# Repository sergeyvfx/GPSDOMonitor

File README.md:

# GPSDO Monitor

A tiny module which is connecting to a databus of GPSDO modules with the goal
to visualize when the PLL is locked, GPS time is stabilized and things like
this. Pretty much minimized version of Lady Heather from John Miles, KE5FX
implemented in microcontroller.

## Licensing

All the work done and implemented for this project is licensed under the
terms of MIT license.

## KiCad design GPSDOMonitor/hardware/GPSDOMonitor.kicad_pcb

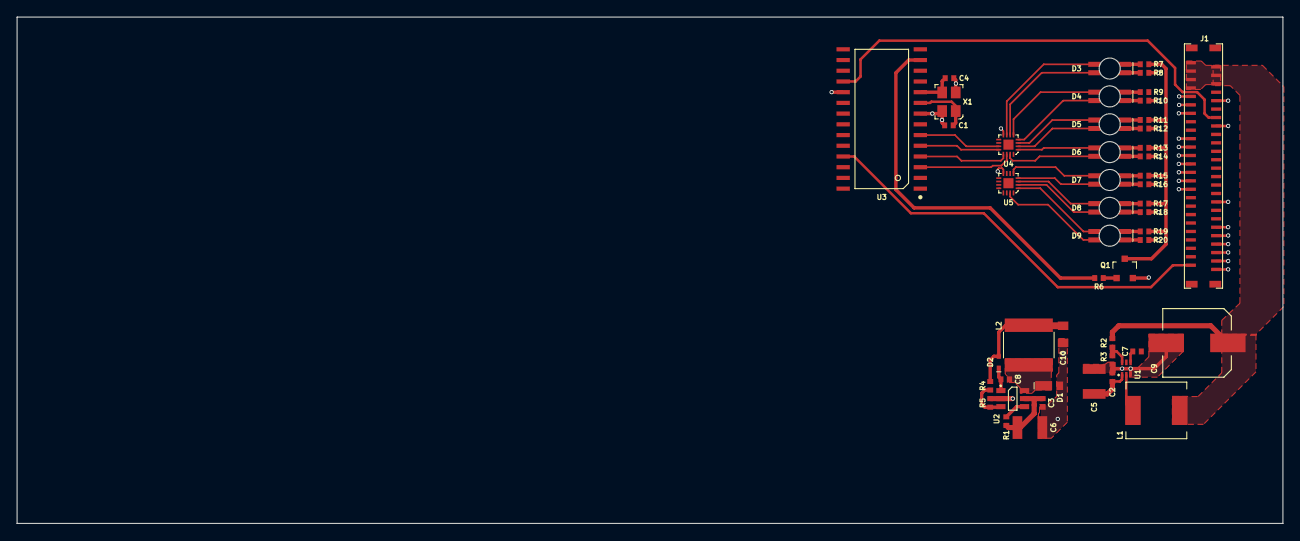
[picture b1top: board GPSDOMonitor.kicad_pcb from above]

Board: 2 copper layers, 150.0 x 60.0 mm, 49 parts (0 on the bottom side), 51 nets.

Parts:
C1, C4: CBR04C409B5GAC; C_0402_1005Metric
C2, C3, C7, C8: UMK105B7104KV-FR; C_0402_1005Metric
C5, C6: UMK325AB7106KM-P; C_1210_3225Metric
C9: A768KE686M1GLAE038; CP_Elec_KEMET_8mm
C10: EMK212BB7106KG-T; C_0805_2012Metric
D1: SS14HE; SOD-323HE
D2: 1N914BWT; SOD-523
D3, D4, D5, D6, D7, D8, D9: 5977703607F
J1: F31S-1A7L1-11050
L1: ASPI-7318-4R7M-T; ASPI-7318
L2: NR6028T150M; NR6028
Q1: MMBT3904LT1G; SOT-23
R1: CRG0402ZR; R_0402_1005Metric
R2: CRGCQ0402F82K; R_0402_1005Metric
R3, R5: CRGCQ0402F10K; R_0402_1005Metric
R4: CRGCQ0402F33K; R_0402_1005Metric
R6: CRGCQ0402F1K0; R_0402_1005Metric
R7, R8, R9, R10, R11, R12, R13, R14, R15, R16, R17, R18, R19, R20: CRGCQ0402F68R; R_0402_1005Metric
U1: TPS563231DRLR; SOT-563
U2: MCP16301T-I_CHY; SOT-23-6
U3: PIC18LF2550-ISO; SOIC-28_Width7.50mm_Pitch1.27mm
U4, U5: SN74HC595BRWNR; X1QFN-16_EP_2.5x2.5mm
X1: ABM8W-20.0000MHZ-4-K1Z-T3; Crystal_SMD_4Pin_3.2x2.5mm

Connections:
+3V3: C10.1, D2.2, L2.2, R4.1, U3.20, U4.10, U5.10
+5V5: C9.1, J1.1, J1.2, J1.3, J1.4, J1.5, J1.6, J1.7, L1.2, R2.1
+12V: C2.1, C3.1, C5.1, C6.1, R1.1, U1.1, U1.5, U2.5
/LED_PWM: R6.2, U3.13
/OE: U3.4, U4.13, U5.13
/RCLK: U3.5, U4.12, U5.12
/SER: U3.3, U4.14
/SRCLK: U3.6, U4.11, U5.11
GND: C1.2, C2.2, C3.2, C4.2, C5.2, C6.2, C9.2, C10.2, D1.2, J1.9, J1.10, J1.11, J1.13, J1.16, J1.19, J1.21, J1.23, J1.25, J1.27, J1.29, J1.31, J1.34, J1.40, J1.42, J1.44, J1.46, J1.48, J1.50, Q1.2, R3.2, R5.2, R8.2, R10.2, R12.2, R14.2, R16.2, R18.2, R20.2, U1.3, U2.2, U3.8, U3.19, U4.8, U5.8, X1.2, X1.4
unnamed: C1.1, U3.9, X1.1
unnamed: C4.1, U3.10, X1.3
unnamed: C7.1, U1.4
unnamed: C7.2, L1.1, U1.2
unnamed: C8.1, D2.1, U2.1
unnamed: C8.2, D1.1, L2.1, U2.6
unnamed: D3.1, R8.1
unnamed: D3.2, U4.6
unnamed: D3.3, U4.7
unnamed: D3.4, R7.1
unnamed: D4.1, R10.1
unnamed: D4.2, U4.4
unnamed: D4.3, U4.5
unnamed: D4.4, R9.1
unnamed: D5.1, R12.1
unnamed: D5.2, U4.2
unnamed: D5.3, U4.3
unnamed: D5.4, R11.1
unnamed: D6.1, R14.1
unnamed: D6.2, U4.15
unnamed: D6.3, U4.1
unnamed: D6.4, R13.1
unnamed: D7.1, R16.1
unnamed: D7.2, U5.4
unnamed: D7.3, U5.5
unnamed: D7.4, R15.1
unnamed: D8.1, R18.1
unnamed: D8.2, U5.2
unnamed: D8.3, U5.3
unnamed: D8.4, R17.1
unnamed: D9.1, R20.1
unnamed: D9.2, U5.15
unnamed: D9.3, U5.1
unnamed: D9.4, R19.1
unnamed: Q1.1, R6.1
unnamed: Q1.3, R7.2, R9.2, R11.2, R13.2, R15.2, R17.2, R19.2
unnamed: R1.2, U2.4
unnamed: R2.2, R3.1, U1.6
unnamed: R4.2, R5.1, U2.3
unnamed: U4.9, U5.14
UART3_TxD: J1.14, U3.18
UART4_TX: J1.49, U3.25

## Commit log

2021-03-06 Initial commit
    Implements timecode and debug protocol parser on PIC18F2550 and logs
    GPSDO status to the pic's UART.
2021-03-07 Add missing MplabX project
2021-03-07 Add gitignore file
2021-03-07 Add missing project XML files
2021-03-07 Change directory layout
    Make it consistent with other electornics project.
    Allows to use own KiCAD library for the hardware part.
2021-03-07 Add readme and license files
2021-03-07 Add KiCAD library
2021-03-07 Add clang-format
2021-03-14 Initial commit of hardware part
    Puts KiCAD project in place, defines common part of microcontroller.
2021-03-20 Add connector for the GPSDO
2021-03-21 Add 5.5v regulator schematic
2021-03-21 Add 3.3v regulator for main CPU logic
2021-04-05 Update project files
    Would be nice to find a way which will keep project
    correct but will not require updating these files on
    every re-save.
2021-04-05 Fix comment in UART module
2021-04-05 Switch debug protocol to Timer3
    Frees up Timer2 to be used for PWM.
2021-04-05 Configure PWM
    Currently unused for anything other than debug purposes.
2021-04-05 Fix incorrect interrupt enable/flag check
2021-04-05 Fix wrong GPS time detection
    Need to ignore timecode from the debug protocol, as it contains
    GPS time which is one second in the future.
2021-04-05 Add safe guards in high priority ISR
2021-04-11 Add shift registers for indication
2021-04-11 Route power supplies
2021-04-11 Correct +5v5 fill zone
2021-04-11 Route majority of the current board
2021-06-13 Use relative path for library
2023-06-17 Ensure manipulation with FSR does not conflict
    Seems that changes in FSR register done from the interrupt
    handler function are not automatically restored, so do it
    explicitly.
    Solves memory corruption caused by UART print which seems to
    be using the same register.
2023-06-17 Ensure transmission is finished before starting new one
    Possibly fixes transmitted string over the UART, which was
    sometimes corrupted.
2023-06-17 Cleanup: Typo
2023-06-17 Add counter to GPSDO status
    Allows to more detect new available data even when no
    fields changed.
2023-06-17 Make memory debugging easier
    - Pass buffer sized when known
    - Add macro which will cause panic on check failure
    Should be no functional changes.
2023-06-17 Update files after recent re-compilation
    Probably should not be updating all of them, but need to
    check which of the changes are actually coming from
    generated files.
2023-06-17 Changes to visualize status using 4 dual-color LEDs
